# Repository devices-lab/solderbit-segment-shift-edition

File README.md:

# solder:bit Segment _Shift Edition_

The solder:bit Segment _Shift Edition_ is a variant of the original [solder:bit Segment](https://github.com/devices-lab/solderbit-segment), designed for learning to solder both surface-mount (SMT) and through-hole (THT) components. Once assembled, it can display a single digit on a 7-segment display, driven by an 8-bit serial-in parallel-out (SIPO) shift register.

This soldering kit is designed to accommodate a wide range of soldering abilities. The shift register is available in two different packages. The 74HC595D in the **SOP-16** package is smaller and more challenging to solder, while the SN74HC595N in the **DIP-16** package is larger and through-hole (THT), making it more accessible for novices. The same printed circuit board (PCB) has footprints for both packages, and you choose which component to solder based on your ability. The device functions identically regardless of which package you use. Note that once you have soldered one package, the footprint for the other will no longer be accessible.

| Shift register in an SOP-16 package (SMT) | Shift register in a DIP-16 package (THT) |
| ----------------------------------------- | ---------------------------------------- |
|              |             |

## Getting started

> [!WARNING]
> This device is a research prototype and is provided as-is. Use it at your own risk. The authors take no responsibility for any damage, injury, or loss arising from its use.

To get started, you will need the following:

1. The printed circuit boards (PCBs), which you will need to have manufactured.
2. All components listed in the bill of materials (BOM).
3. A microcontroller development board, like the BBC micro:bit.
4. All equipment and materials required for soldering.

### Printed circuit boards (PCBs)

The solder:bit Segment _Shift Edition_ fabrication files are open source, so you can order the PCBs yourself!

To fabricate the PCB, use the files in the [gerbers-v0.1](/fabrication/gerbers-v0.1/) folder.

### Components

> [!NOTE]
> Most of these components are sourced from [Onecall (Farnell/CPC)](https://onecall.farnell.com/) and [LCSC](https://lcsc.com), but as they are fairly common components, alternatives can be found from other suppliers such as DigiKey and others.

| Reference | Quantity | Part            | Package      | Onecall order code | LCSC part number                                              |
| --------- | -------- | --------------- | ------------ | ------------------ | ------------------------------------------------------------- |
| C1        | 1        | 1 µF \*         | 1206         | 3188966            | [C1848](https://www.lcsc.com/product-detail/C1848.html)       |
| DS1       | 1        | SM420561N \*    | Through Hole | 3648330            | [C141367](https://www.lcsc.com/product-detail/C141367.html)   |
| J1        | 1        | 8-pin header \* | 2.54mm, THT  | 1593416            | [C492407](https://www.lcsc.com/product-detail/C492407.html)   |
| R1, R2    | 2        | 100 kΩ \*       | 1206         | 9241060            | [C17900](https://www.lcsc.com/product-detail/C17900.html)     |
| R3–R10    | 8        | 300 Ω \*        | 1206         | 9240420            | [C17887](https://www.lcsc.com/product-detail/C17887.html)     |
| U1        | 1        | 74HC595D        | SOP-16       | 1201269            | [C5144558](https://www.lcsc.com/product-detail/C5144558.html) |
| U2        | 1        | SN74HC595N      | DIP-16       | 3120865            | [C507175](https://www.lcsc.com/product-detail/C507175.html)   |

_\* Generic component; the order code is provided as a reference, but any equivalent component in the same package can be substituted._

Note that U1 and U2 are alternative packages for the same 74HC595 component — you only need one. You can source both and choose whichever you are more comfortable soldering.

The 7-segment display(s) listed above has red segments. If you would like other colours, note that you might need to adjust R3-R10 resistor values. Also note that you will need a larger resistor value (at least 350 Ω) if you are powering the device with 5 V instead of 3.3 V. This is to ensure the output current from all output pins on the shift register doesn't exceed 70 mA in total.

Depending on how you plan to connect the solder:bit Segment _Shift Edition_ to your microcontroller development board, you may also need a breadboard and some jumper cables.

### Development board

You can use a BBC micro:bit to control the solder:bit Segment _Shift Edition_. Once assembled, attach the device to a breadboard, plug the micro:bit into a [breadboard adaptor](https://kitronik.co.uk/products/5664-microbit-breadboard-breakout-board), and connect it to the breadboard. See the [programming](#programming) section below to see how to wire it up.

> [!CAUTION]
> The device operates at supply voltages (VDD) between 2.1 V and 6 V. When running at 5 V or higher, resistors R3-R10 must be at least 350 Ω to keep the current within safe limits.

The solder:bit Segment _Shift Edition_ can also be used with other microcontroller development boards such as the [Raspberry Pi Pico](https://www.raspberrypi.com/products/raspberry-pi-pico/) or [Arduino Uno](https://store.arduino.cc/products/arduino-uno-rev3), however we currently only provide programming support for the micro:bit.

See the [programming](#programming) section below for how to write code to control the solder:bit Segment _Shift Edition_.

### Equipment and materials for soldering

The required equipment will vary depending on your soldering setup and needs, but the following is what you will generally need:

- Safety goggles
- Fume extractor fan
- Soldering iron
- Soldering iron stand
- Brass wool
- Silicone mat
- Solder
- Tweezers
- Solder wick

The following items are optional but useful:

- Blue Tack (for keeping the PCB in place)
- PCB holder/helping hands
- Flux
- Tip cleaner
- Desoldering pump
- Isopropyl alcohol (IPA) and cotton swabs
- Multimeter (for checking continuity in solder joints)

> [!CAUTION]
> To minimise health hazards, we recommend using lead-free and rosin-free solder and flux.

> [!TIP]
> If you are running this as a workshop/event activity, an [HDMI digital microscope](https://www.amazon.co.uk/dp/B09VPPS96M) connected to a display is very useful for streaming a soldering demonstration to the entire room.

> [!TIP]
> Smaller soldering iron tips make it easier to reach tight spaces, but they transfer heat less effectively. We recommend trying out a few different tip sizes and choosing one that works well with your soldering iron.

## Assembly instructions

Coming soon...

## Programming

If you are using a BBC micro:bit, you can program the solder:bit Segment _Shift Edition_ in [MakeCode](https://makecode.microbit.org/) using the [pxt-solderbit-segment](https://github.com/devices-lab/pxt-solderbit-segment) extension.

You can test if your assembled device works by flashing the micro:bit with the [demo file](/demo/microbit-solderbit-segment-shift-edition-demo.hex). Attach the solder:bit Segment _Shift Edition_ to a breadboard, insert the micro:bit into a [breadboard adaptor](https://kitronik.co.uk/products/5664-microbit-breadboard-breakout-board), and plug it into the breadboard. Connect the device to the micro:bit using the following pinout:

| solder:bit Segment _Shift Edition_ | BBC micro:bit |
| ---------------------------------- | ------------- |
| GND                                | GND           |
| VCC                                | 3V            |
| STCP                               | P2            |
| SHCP                               | P1            |
| DS                                 | P0            |

See [this image](/demo/wiring_front.jpeg) for an example of how to wire it up.

For any other development board, you will need to write the firmware yourself. Refer to the [solder:bit Segment Shift Edition schematic](/reference/solderbit%20Segment%20Shift%20Edition%20v0.1%20schematic.pdf), the datasheets for the I/O expanders (both packages), and the 7-segment display datasheet, all of which are available in the [reference](/reference/) folder.

> [!NOTE]
> The [pxt-solderbit-segment](https://github.com/devices-lab/pxt-solderbit-segment) MakeCode extension handles the original solder:bit Segment as well as this newer solder:bit Segment _Shift Edition_.

## Project status and contributing

This project is actively maintained. See [CHANGELOG.md](/CHANGELOG.md) for the latest changes.

At this time, external contributions are not being accepted. If you have suggestions or have found an issue, feel free to open a GitHub issue and we will take a look.

## Contact

If you are interested in using solder:bit kits for your classroom, university, conference, or any other workshop or event, feel free to reach out to me @mac-aron or contact [Devices Lab](https://devices-lab.org/contact).

## Acknowledgements

Special thanks to everyone at the [Devices Lab](https://www.devices-lab.org/) for their ongoing support on this project and for their help running soldering workshops.

## License

This project is licensed under the GNU General Public License (GPL), version 3. This license allows you to use, modify, and redistribute the solder:bit Segment _Shift Edition_ and any derivative works, but all such derivatives must also be licensed under the GPL.

The GPL ensures that all modifications and improvements to the solder:bit Segment _Shift Edition_ remain free and open for the public benefit. By using this project, you agree to abide by its terms and conditions.

For more details on the license, please see the [LICENSE](/LICENSE) file included in this repository.

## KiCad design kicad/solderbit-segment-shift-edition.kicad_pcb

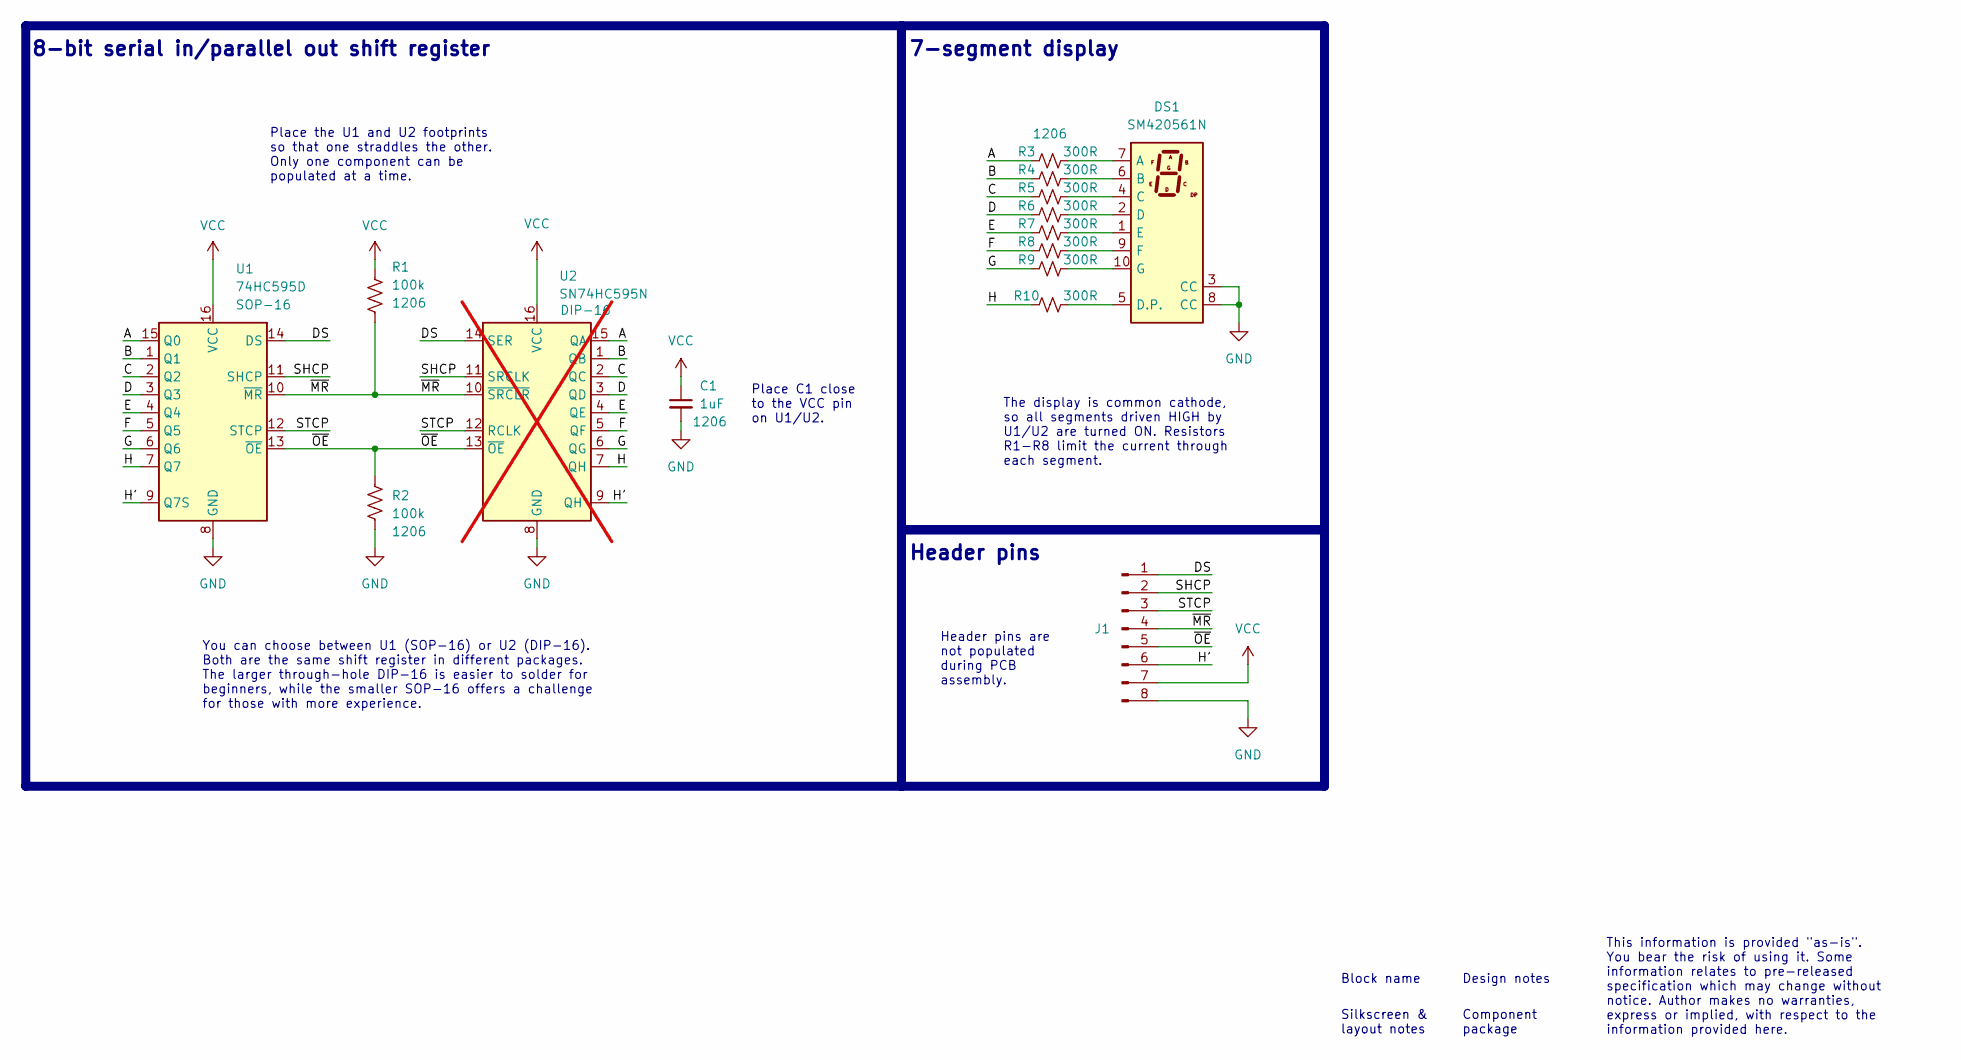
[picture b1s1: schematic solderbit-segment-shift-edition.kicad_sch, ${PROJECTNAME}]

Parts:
C1: 1uF; C_1206; LCSC Part C1848
DS1: SM420561N; DISPLAY_7SEGMENT_0.56__THT; LCSC Part C141367
J1: Conn_01x08_Pin; PinHeader_1x08_P2.54mm_Vertical; LCSC Part C492407
R1, R2: 100k; R_1206; LCSC Part C17900
R3, R4, R5, R6, R7, R8, R9, R10: 300R; R_1206; LCSC Part C17887
U1: 74HC595D; SOIC-16_3.9x9.9mm_P1.27mm; LCSC Part C5144558
U2: SN74HC595N; DIP-16_W7.62; LCSC Part C507175; not fitted

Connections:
/A: R3.1, U1.15 (Q0), U2.15 (QA)
/B: R4.1, U1.1 (Q1), U2.1 (QB)
/C: R5.1, U1.2 (Q2), U2.2 (QC)
/D: R6.1, U1.3 (Q3), U2.3 (QD)
/DS: J1.1, U1.14 (DS), U2.14 (SER)
/E: R7.1, U1.4 (Q4), U2.4 (QE)
/F: R8.1, U1.5 (Q5), U2.5 (QF)
/G: R9.1, U1.6 (Q6), U2.6 (QG)
/H: R10.1, U1.7 (Q7), U2.7 (QH)
/H': J1.6, U1.9 (Q7S), U2.9 (QH')
/SHCP: J1.2, U1.11 (SHCP), U2.11 (SRCLK)
/STCP: J1.3, U1.12 (STCP), U2.12 (RCLK)
/~MR: J1.4, R1.2, U1.10 (~MR), U2.10 (~SRCLR)
/~OE: J1.5, R2.1, U1.13 (~OE), U2.13 (~OE)
GND: C1.2, DS1.3 (CC), DS1.8 (CC), J1.8, R2.2, U1.8 (GND), U2.8 (GND)
unnamed: DS1.7 (A), R3.2
unnamed: DS1.6 (B), R4.2
unnamed: DS1.4 (C), R5.2
unnamed: DS1.2 (D), R6.2
unnamed: DS1.5 (D.P.), R10.2
unnamed: DS1.1 (E), R7.2
unnamed: DS1.9 (F), R8.2
unnamed: DS1.10 (G), R9.2
VCC: C1.1, J1.7, R1.1, U1.16 (VCC), U2.16 (VCC)

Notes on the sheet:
Silkscreen & layout notes
Component package
Place the U1 and U2 footprints so that one straddles the other. Only one component can be populated at a time.
Header pins are not populated during PCB assembly.
The display is common cathode, so all segments driven HIGH by U1/U2 are turned ON. Resistors R1-R8 limit the current through each segment.
You can choose between U1 (SOP-16) or U2 (DIP-16). Both are the same shift register in different packages. The larger through-hole DIP-16 is easier to solder for beginners, while the smaller SOP-16 offers a challenge for those with more experience.
Header pins
Block name
This information is provided "as-is". You bear the risk of using it. Some information relates to pre-released specification which may change without notice. Author makes no warranties, express or implied, with respect to the information provided here.
7-segment display
8-bit serial in/parallel out shift register
Place C1 close to the VCC pin on U1/U2.
Design notes

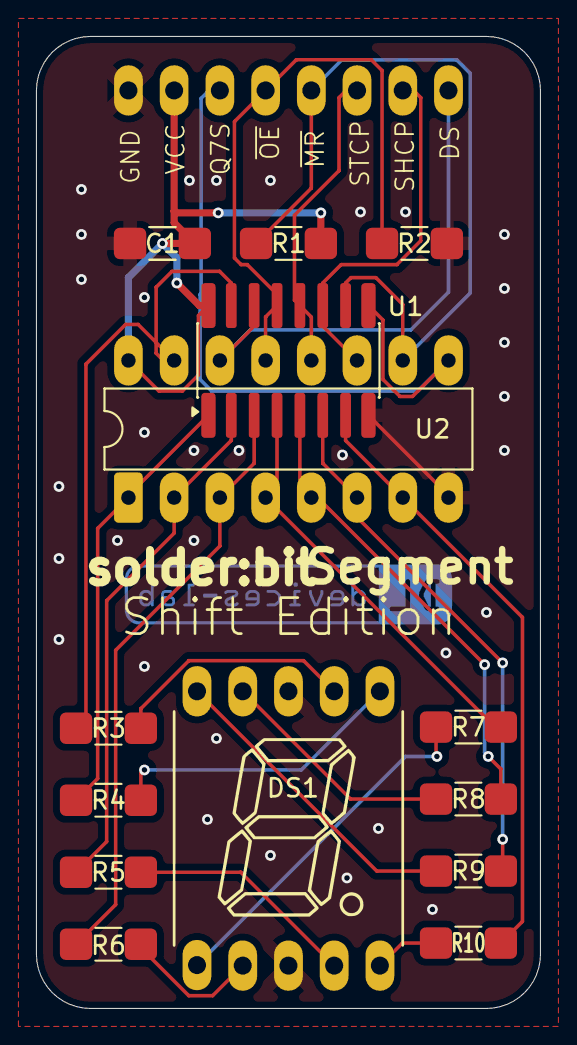
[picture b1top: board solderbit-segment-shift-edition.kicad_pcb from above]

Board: 2 copper layers, 28.0 x 54.0 mm, 15 parts (1 on the bottom side), 24 nets.

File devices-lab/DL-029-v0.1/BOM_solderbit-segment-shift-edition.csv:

"Reference","Value","Package","LCSC Part"
"U1","74HC595D","SOP-16","C5144558"
"R3,R4,R5,R6,R7,R8,R9,R10","300R","1206","C17887"
"R1,R2","100k","1206","C17900"
"DS1","SM420561N","Through Hole","C141367"
"C1","1uF","1206","C1848"

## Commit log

2026-04-21 Update all documentation
2026-04-21 Gerber files
2026-04-21 Update LICENSE file
2026-04-22 Update device renders with green silkscreen
2026-04-22 KiCad 10 first save
2026-04-29 Assembly images
2026-04-29 Remove DNP flag for header pins
2026-04-29 Export an updated schematic
2026-04-29 Full assembly images
